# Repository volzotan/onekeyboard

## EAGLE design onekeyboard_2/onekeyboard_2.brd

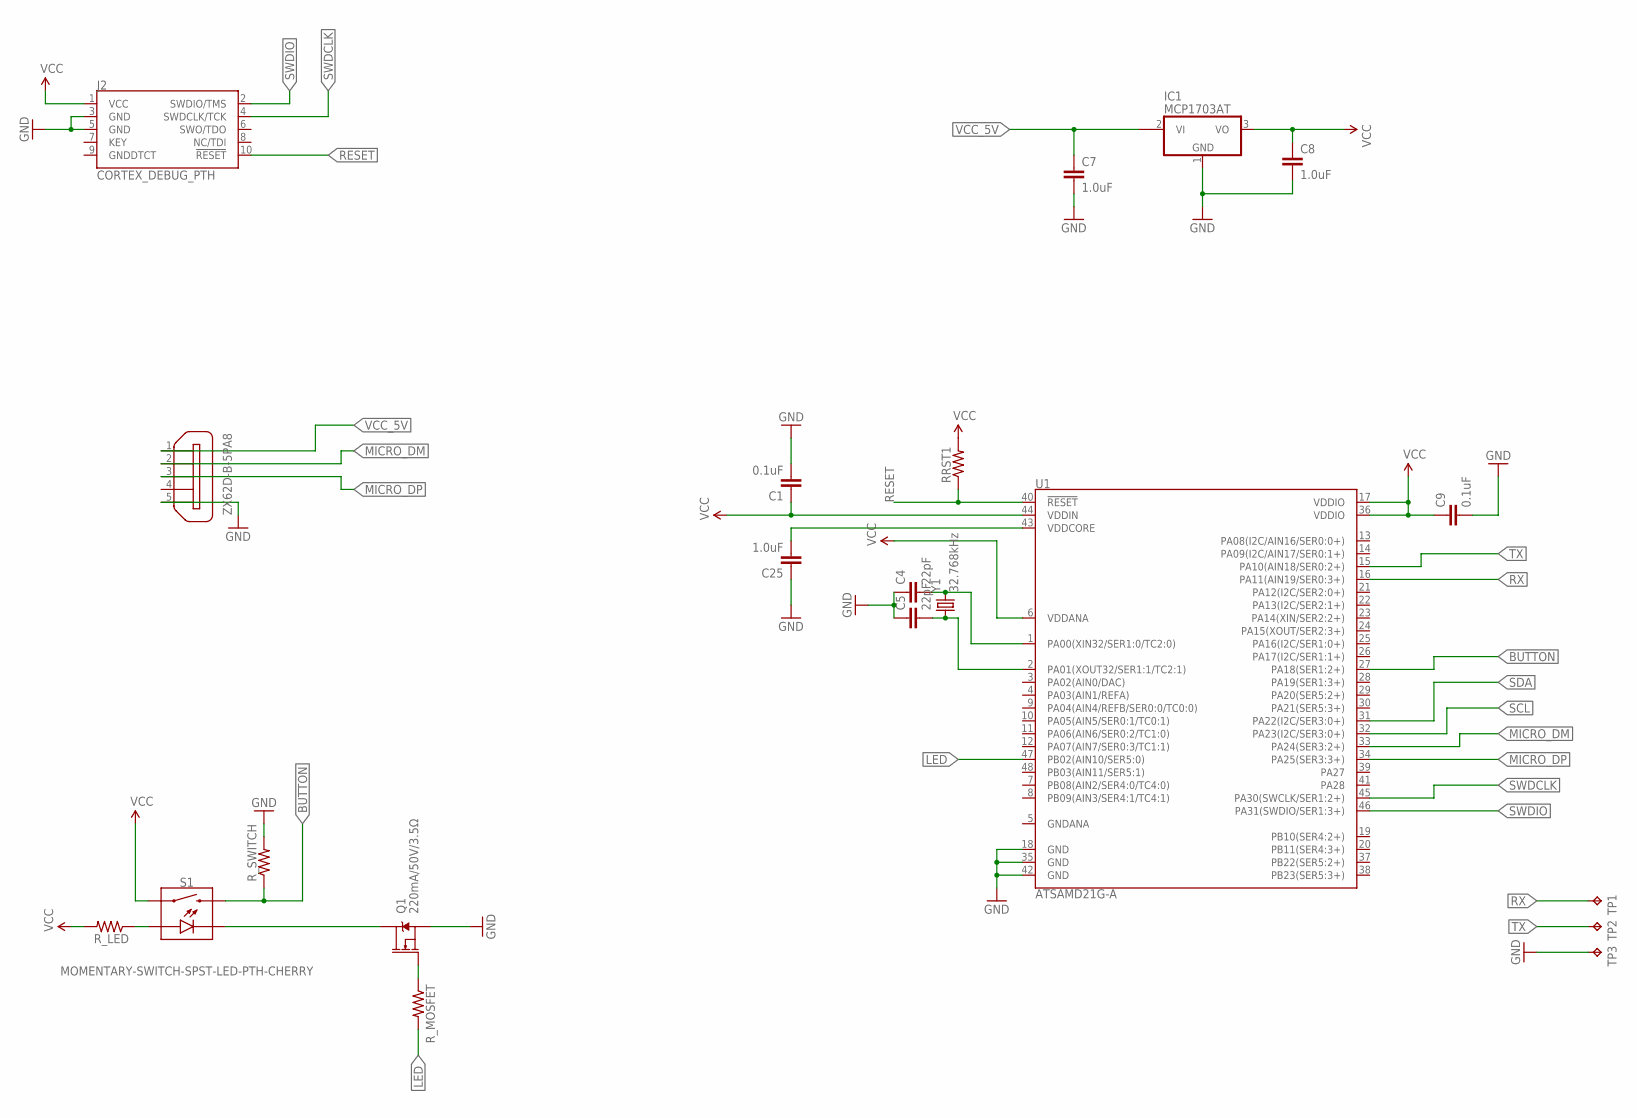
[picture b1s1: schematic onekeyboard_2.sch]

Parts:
C1, C9: 0.1uF; 0805
C4, C5: 22pF; 0805
C7, C8: 1.0uF; 1206
C25: 1.0uF; 0805
IC1: MCP1703AT; SOT89
J2: CORTEX_DEBUG_PTH; 2X5-PTH-1.27MM
Q1: 220mA/50V/3.5Ω; SOT23-3
RRST1: RESISTOR0805-RES; 0805
R_LED: RESISTOR0805-RES; 0805
R_MOSFET: RESISTOR0805-RES; 0805
R_SWITCH: RESISTOR0805-RES; 0805
S1: MOMENTARY-SWITCH-SPST-LED-PTH-CHERRY; CHERRY-MX-LED
TP1, TP2, TP3: TPB2,54; B2,54
U1: ATSAMD21G-A; TQFP-48
X2: ZX62D-B-5PA8
Y1: 32.768kHz; CRYSTAL-SMD-3.2X1.5MM

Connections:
BUTTON: R_SWITCH.1, S1.S2 (2), U1.27 (PA18(SER1:2+))
GND: C1.2, C4.1, C5.1, C7.2, C8.2, C9.2, C25.1, IC1.1 (GND), J2.3 (GND), J2.5 (GND), Q1.2 (S), R_SWITCH.2, TP3.TP, U1.18 (GND), U1.35 (GND), U1.42 (GND), X2.5
LED: R_MOSFET.2, U1.47 (PB02(AIN10/SER5:0))
MICRO_DM: U1.33 (PA24(SER3:2+)), X2.2
MICRO_DP: U1.34 (PA25(SER3:3+)), X2.3
unnamed: R_LED.1, S1.A
unnamed: Q1.1 (G), R_MOSFET.1
unnamed: Q1.3 (D), S1.K (C)
unnamed: C25.2, U1.43 (VDDCORE)
unnamed: C4.2, U1.1 (PA00(XIN32/SER1:0/TC2:0)), Y1.P$2 (2)
unnamed: C5.2, U1.2 (PA01(XOUT32/SER1:1/TC2:1)), Y1.P$1 (1)
RESET: J2.10 (!RESET), RRST1.1, U1.40 (!RESET!)
RX: TP1.TP, U1.16 (PA11(AIN19/SER0:3+))
SCL: U1.32 (PA23(I2C/SER3:0+))
SDA: U1.31 (PA22(I2C/SER3:0+))
SWDCLK: J2.4 (SWDCLK/TCK), U1.45 (PA30(SWCLK/SER1:2+))
SWDIO: J2.2 (SWDIO/TMS), U1.46 (PA31(SWDIO/SER1:3+))
TX: TP2.TP, U1.15 (PA10(AIN18/SER0:2+))
VCC: C1.1, C8.1, C9.1, IC1.3 (VO), J2.1 (VCC), RRST1.2, R_LED.2, S1.S1 (1), U1.6 (VDDANA), U1.17 (VDDIO), U1.36 (VDDIO), U1.44 (VDDIN)
VCC_5V: C7.1, IC1.2@1 (VI1), X2.1

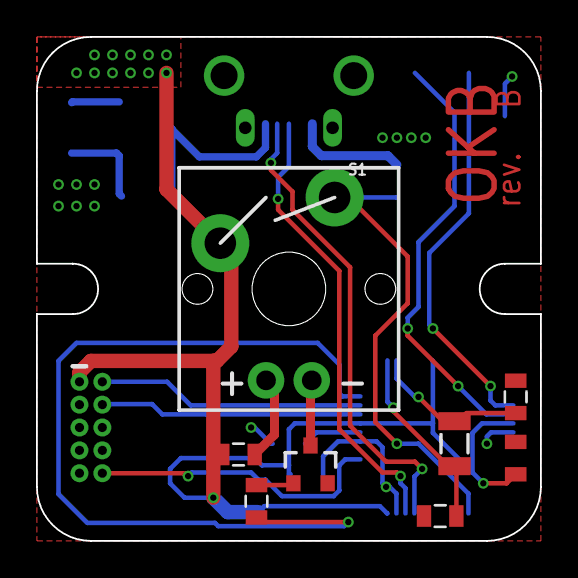
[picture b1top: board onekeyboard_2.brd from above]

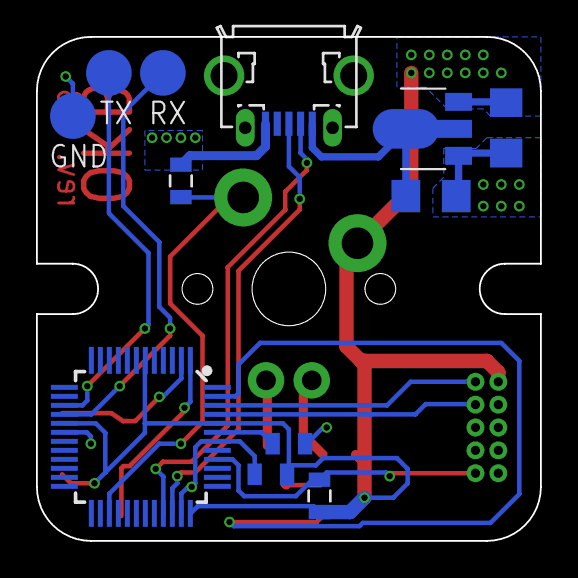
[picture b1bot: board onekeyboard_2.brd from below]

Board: 2 copper layers, 28.0 x 28.0 mm, 21 parts (12 on the bottom side), 18 nets.

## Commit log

2019-11-12 sent to fab
2019-12-09 firmware
2020-02-02 revB firmware
2020-02-02 rev B eagle files
2020-02-02 cleanup

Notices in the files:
parts and their libraries:
SparkFun-Passives: Licensing: Creative Commons ShareAlike 4.0 International - https://creativecommons.org/licenses/by-sa/4.0
